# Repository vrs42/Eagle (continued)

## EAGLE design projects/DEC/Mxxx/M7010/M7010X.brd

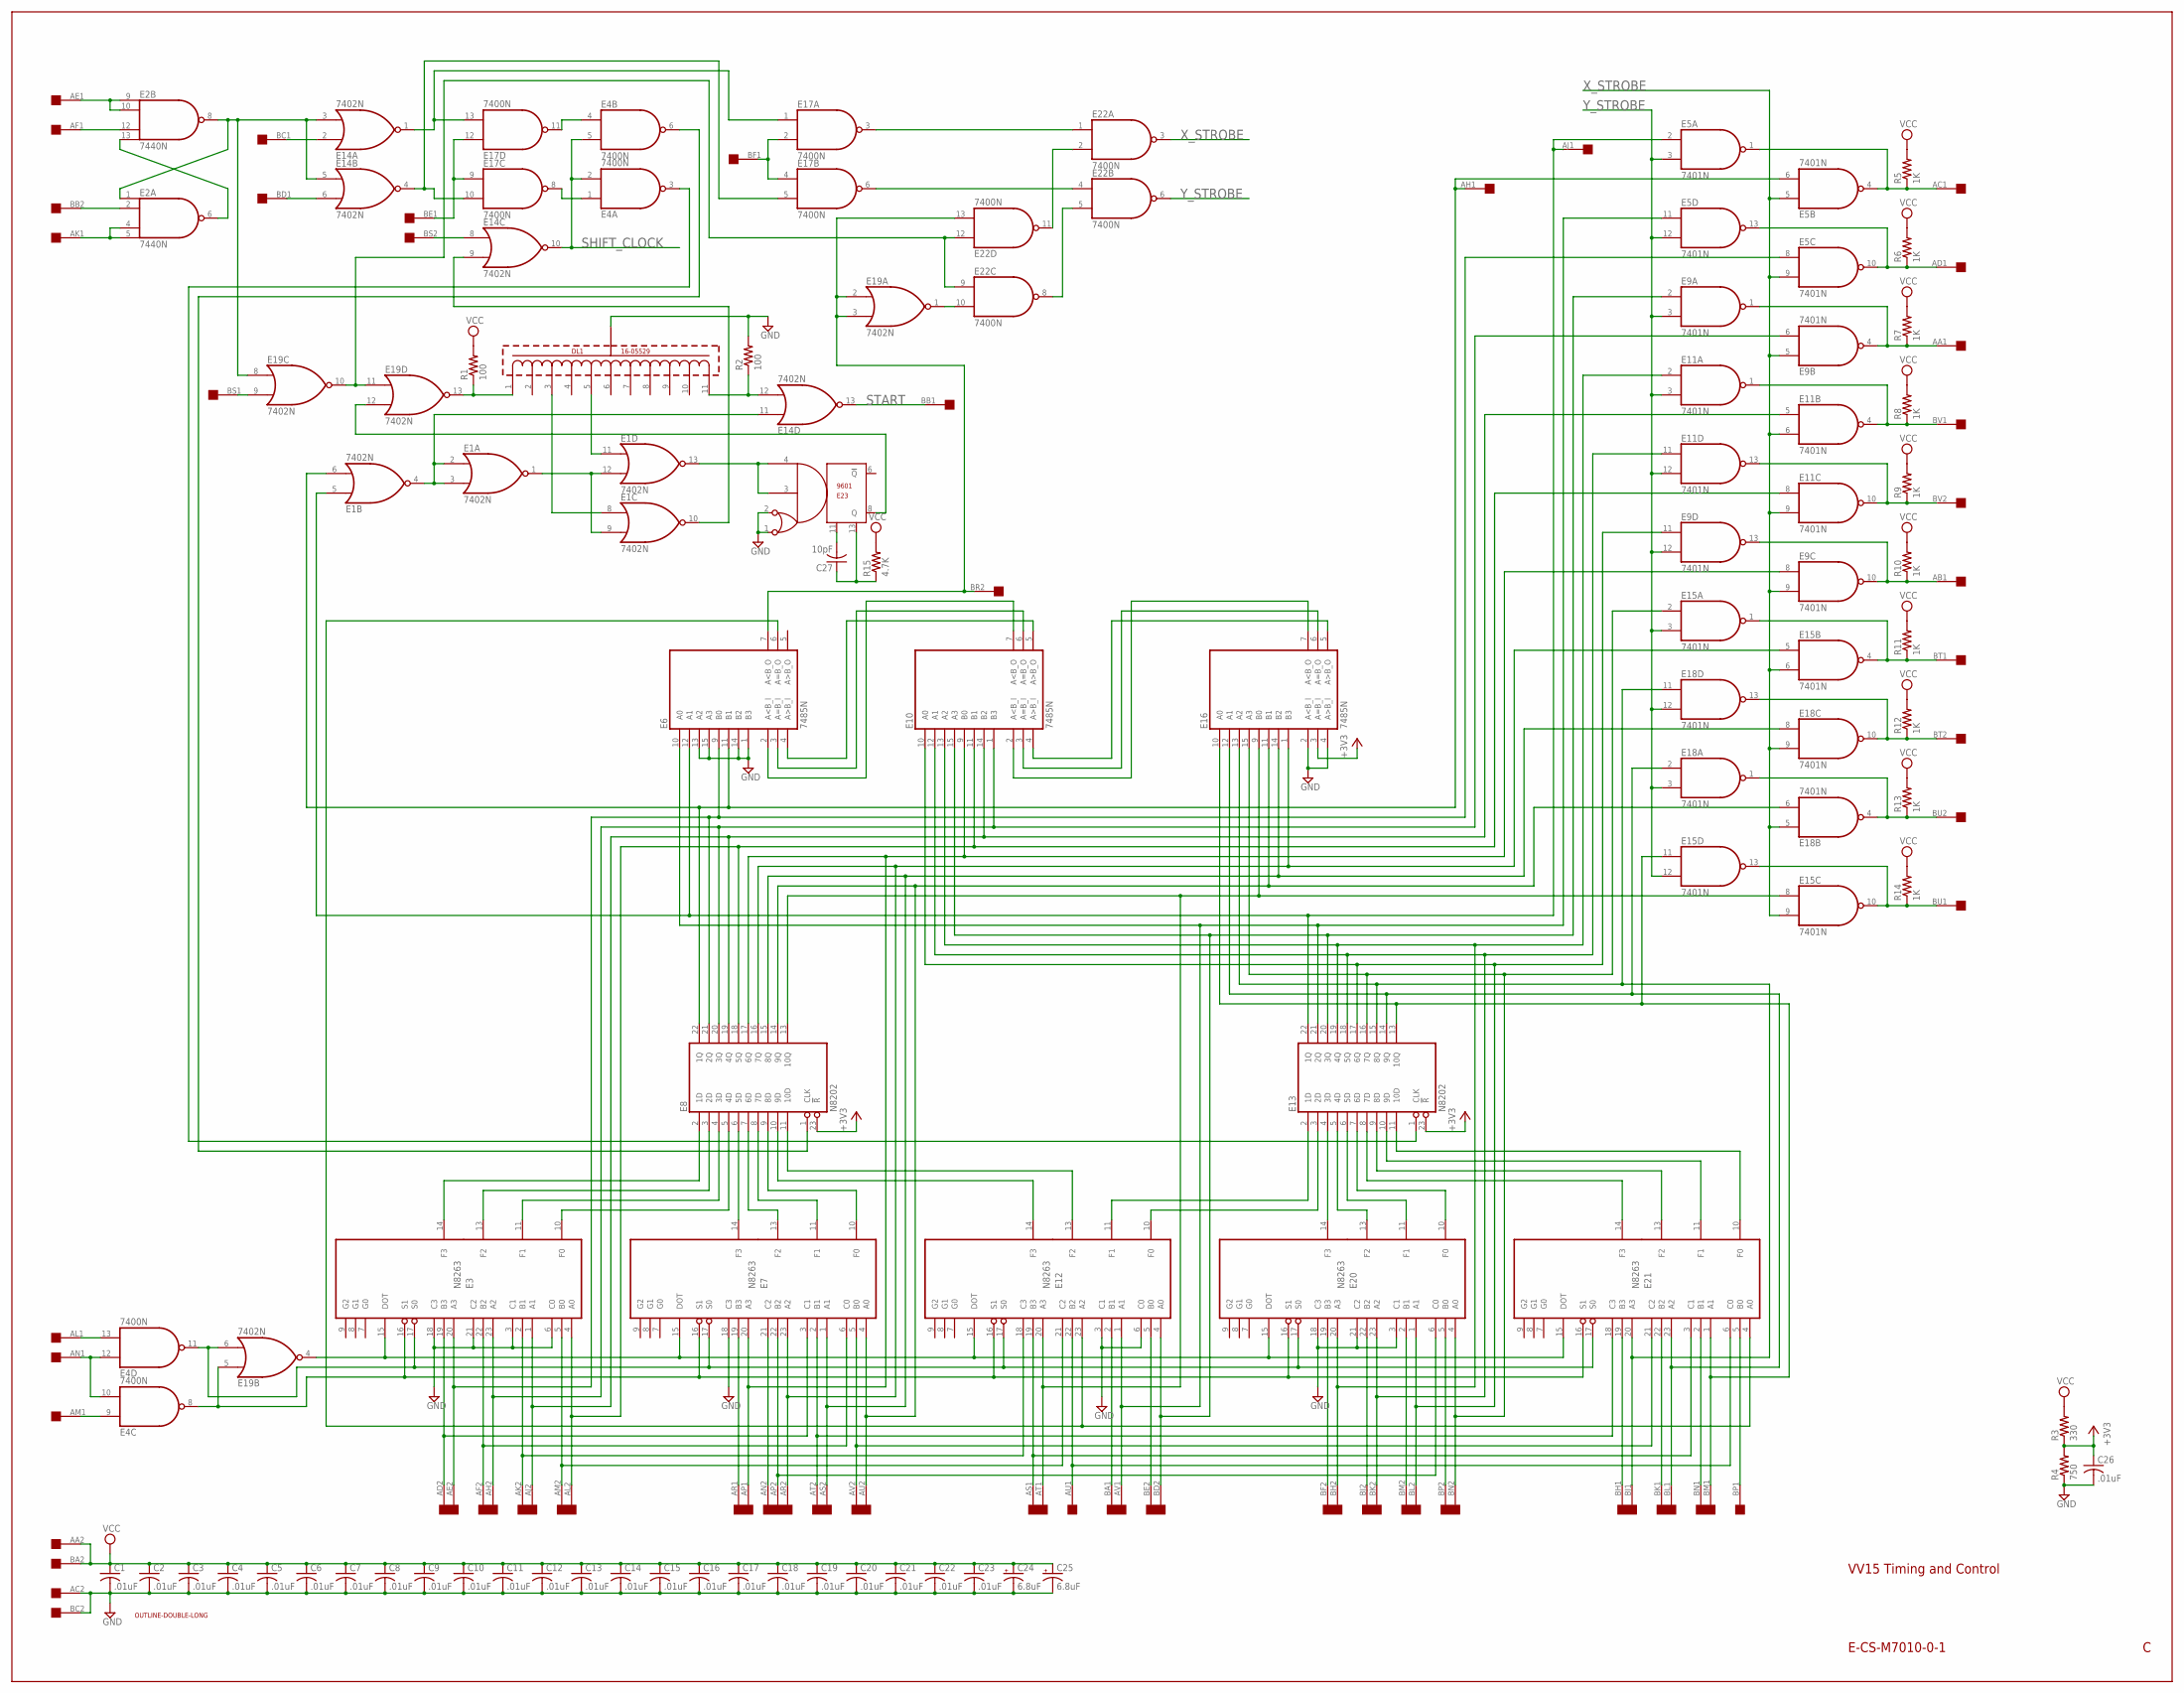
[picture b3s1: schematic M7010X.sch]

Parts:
C1, C2, C3, C4, C5, C6, C7, C8, C9, C10, C11, C12, C13, C14, C15, C16, C17, C18, C19, C20, C21, C22, C23, C26: .01uF; C050-025X075
C24, C25: 6.8uF; E12-8
C27: 10pF; C050-025X075
DL1: 16-05529
E1, E14, E19: 7402N; DIL14
E2: 7440N; DIL14
E3, E7, E12, E20, E21: N8263; DIL24
E4, E17, E22: 7400N; DIL14
E5, E9, E11, E15, E18: 7401N; DIL14
E6, E10, E16: 7485N; DIL16
E8, E13: N8202; DIL24
E23: 9601; DIL14
R1, R2: 100; 0207/10
R3: 330; 0207/10
R4: 750; 0207/10
R5, R6, R7, R8, R9, R10, R11, R12, R13, R14: 1K; 0207/10
R15: 4.7K; 0207/10
U$1: OUTLINE-DOUBLE-LONG; DOUBLE-LONG
U$3: DOUBLE; EDGE-CON4

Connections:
+3V3: C26.1, E8.23 (!R), E13.23 (!R), E16.3 (A=B_I), R3.1, R4.2
GND: C1.2, C2.2, C3.2, C4.2, C5.2, C6.2, C7.2, C8.2, C9.2, C10.2, C11.2, C12.2, C13.2, C14.2, C15.2, C16.2, C17.2, C18.2, C19.2, C20.2, C21.2, C22.2, C23.2, C24.-, C25.-, C26.2, DL1.12 (GND), E1.7 (GND), E2.7 (GND), E3.3 (C1), E3.6 (C0), E3.12 (GND), E3.18 (C3), E3.21 (C2), E4.7 (GND), E5.7 (GND), E6.1 (B3), E6.8 (GND), E6.13 (A2), E6.14 (B2), E6.15 (A3), E7.12 (GND), E7.18 (C3), E8.12 (GND), E9.7 (GND), E10.8 (GND), E11.7 (GND), E12.3 (C1), E12.6 (C0), E12.12 (GND), E13.12 (GND), E14.7 (GND), E15.7 (GND), E16.2 (A<B_I), E16.4 (A>B_I), E16.8 (GND), E17.7 (GND), E18.7 (GND), E19.7 (GND), E20.3 (C1), E20.12 (GND), E20.18 (C3), E20.21 (C2), E21.12 (GND), E22.7 (GND), E23.1, E23.2, E23.7 (GND), R2.2, R4.1, U$3.AC2, U$3.BC2
unnamed: E3.20 (A3), E5.8 (I0), E6.9 (B0), E8.21 (2Q), U$3.AE2
unnamed: E3.23 (A2), E8.20 (3Q), E9.6 (I1), E10.1 (B3), U$3.AH2
unnamed: E3.1 (A1), E8.19 (4Q), E10.14 (B2), E11.5 (I0), U$3.AJ2
unnamed: E3.4 (A0), E8.18 (5Q), E10.11 (B1), E11.8 (I0), U$3.AL2
unnamed: E3.19 (B3), E7.3 (C1), U$3.AD2
unnamed: E3.22 (B2), E7.6 (C0), U$3.AF2
unnamed: E3.2 (B1), E12.18 (C3), U$3.AK2
unnamed: E3.5 (B0), E12.21 (C2), U$3.AM2
unnamed: E7.21 (C2), U$3.AN2
unnamed: E3.15 (DOT), E7.15 (DOT), E12.15 (DOT), E19.4 (O), E20.15 (DOT), E21.15 (DOT)
unnamed: E3.17 (S0), E4.11 (O), E7.17 (S0), E12.17 (S0), E19.6 (I1), E20.17 (S0), E21.17 (S0)
unnamed: E3.16 (S1), E4.8 (O), E7.16 (S1), E12.16 (S1), E19.5 (I0), E20.16 (S1), E21.16 (S1)
unnamed: E7.5 (B0), E21.21 (C2), U$3.AV2
unnamed: E7.2 (B1), E21.18 (C3), U$3.AT2
unnamed: E7.22 (B2), E20.6 (C0), U$3.AP2
unnamed: E7.20 (A3), E8.17 (6Q), E9.8 (I0), E10.9 (B0), U$3.AP1
unnamed: E1.10 (O), E14.9 (I1)
unnamed: E7.1 (A1), E8.15 (8Q), E16.14 (B2), E18.8 (I0), U$3.AS2
unnamed: E7.23 (A2), E8.16 (7Q), E15.5 (I0), E16.1 (B3), U$3.AR2
unnamed: E7.19 (B3), U$3.AR1
unnamed: E7.14 (F3), E8.6 (5D)
unnamed: E7.13 (F2), E8.7 (6D)
unnamed: E7.11 (F1), E8.8 (7D)
unnamed: E7.10 (F0), E8.9 (8D)
unnamed: E3.10 (F0), E8.5 (4D)
unnamed: E3.11 (F1), E8.4 (3D)
unnamed: E3.13 (F2), E8.3 (2D)
unnamed: E3.14 (F3), E8.2 (1D)
unnamed: E8.10 (9D), E12.14 (F3)
unnamed: E8.11 (10D), E12.13 (F2)
unnamed: E13.4 (3D), E20.14 (F3)
unnamed: E13.5 (4D), E20.13 (F2)
unnamed: E13.6 (5D), E20.11 (F1)
unnamed: E13.7 (6D), E20.10 (F0)
unnamed: E12.10 (F0), E13.3 (2D)
unnamed: E12.11 (F1), E13.2 (1D)
unnamed: E13.10 (9D), E21.11 (F1)
unnamed: E13.8 (7D), E21.14 (F3)
unnamed: E13.9 (8D), E21.13 (F2)
unnamed: E13.11 (10D), E21.10 (F0)
unnamed: E5.1 (O), E5.4 (O), R5.1, U$3.AC1
unnamed: E5.10 (O), E5.13 (O), R6.1, U$3.AD1
unnamed: E15.10 (O), E15.13 (O), R14.1, U$3.BU1
unnamed: E18.1 (O), E18.4 (O), R13.1, U$3.BU2
unnamed: E18.10 (O), E18.13 (O), R12.1, U$3.BT2
unnamed: E15.1 (O), E15.4 (O), R11.1, U$3.BT1
unnamed: E9.10 (O), E9.13 (O), R10.1, U$3.AB1
unnamed: E9.1 (O), E9.4 (O), R7.1, U$3.AA1
unnamed: E11.1 (O), E11.4 (O), R8.1, U$3.BV1
unnamed: E11.10 (O), E11.13 (O), R9.1, U$3.BV2
unnamed: E1.2 (I0), E1.3 (I1), E1.4 (O), E14.11 (I0)
unnamed: DL1.11 (50), E14.12 (I1), R2.1
unnamed: E2.1 (I0), E2.8 (O), E14.3 (I1), E14.5 (I0), E19.8 (I0)
unnamed: E1.5 (I0), E5.2 (I0), E6.12 (A1), E13.22 (1Q), U$3.AJ1
unnamed: E1.6 (I1), E5.6 (I1), E6.11 (B1), E8.22 (1Q), U$3.AH1
unnamed: E5.11 (I0), E6.10 (A0), E12.1 (A1), E13.21 (2Q), U$3.AV1
unnamed: E9.2 (I0), E10.15 (A3), E12.4 (A0), E13.20 (3Q), U$3.BD2
unnamed: E10.13 (A2), E11.2 (I0), E13.19 (4Q), E20.20 (A3), U$3.BH2
unnamed: E10.12 (A1), E11.11 (I0), E13.18 (5Q), E20.23 (A2), U$3.BK2
unnamed: E19.9 (I1), U$3.BS1
unnamed: E9.11 (I0), E10.10 (A0), E13.17 (6Q), E20.1 (A1), U$3.BL2
unnamed: E8.13 (10Q), E12.20 (A3), E15.8 (I0), E16.9 (B0), U$3.AT1
unnamed: E13.13 (10Q), E15.11 (I0), E16.10 (A0), E21.1 (A1), U$3.BM1
unnamed: E7.4 (A0), E8.14 (9Q), E16.11 (B1), E18.6 (I1), U$3.AU2
unnamed: E13.14 (9Q), E16.12 (A1), E18.2 (I0), E21.23 (A2), U$3.BL1
unnamed: E13.15 (8Q), E16.13 (A2), E18.11 (I0), E21.20 (A3), U$3.BJ1
unnamed: E13.16 (7Q), E15.2 (I0), E16.15 (A3), E20.4 (A0), U$3.BN2
unnamed: E6.6 (A=B_O), E12.23 (A2), E21.4 (A0)
unnamed: E12.19 (B3), E21.3 (C1), U$3.AS1
unnamed: E12.22 (B2), E21.6 (C0), U$3.AU1
unnamed: E4.13 (I1), U$3.AL1
unnamed: E12.2 (B1), U$3.BA1
unnamed: E12.5 (B0), U$3.BE2
unnamed: E20.19 (B3), U$3.BF2
unnamed: E20.22 (B2), U$3.BJ2
unnamed: E20.2 (B1), U$3.BM2
unnamed: E20.5 (B0), U$3.BP2
unnamed: E21.19 (B3), U$3.BH1
unnamed: E21.22 (B2), U$3.BK1
unnamed: E21.2 (B1), U$3.BN1
unnamed: E21.5 (B0), U$3.BP1
unnamed: E4.9 (I0), U$3.AM1
unnamed: E10.4 (A>B_I), E16.5 (A>B_O)
unnamed: E10.3 (A=B_I), E16.6 (A=B_O)
unnamed: E10.2 (A<B_I), E16.7 (A<B_O)
unnamed: E6.4 (A>B_I), E10.5 (A>B_O)
unnamed: E6.3 (A=B_I), E10.6 (A=B_O)
unnamed: E6.2 (A<B_I), E10.7 (A<B_O)
unnamed: E4.10 (I1), E4.12 (I0), U$3.AN1
unnamed: E14.6 (I1), U$3.BD1
unnamed: E14.2 (I0), U$3.BC1
unnamed: E14.4 (O), E17.5 (I1), E17.10 (I1)
unnamed: E2.9 (I0), E2.10 (I1), U$3.AE1
unnamed: E2.12 (I2), U$3.AF1
unnamed: E2.6 (O), E2.13 (I3)
unnamed: E2.2 (I1), U$3.BB2
unnamed: E2.4 (I2), E2.5 (I3), U$3.AK1
unnamed: E14.1 (O), E17.1 (I0), E17.13 (I1)
unnamed: E17.9 (I0), E17.12 (I0), U$3.BE1
unnamed: E4.1 (I0), E17.8 (O)
unnamed: E4.4 (I0), E17.11 (O)
unnamed: E14.8 (I0), U$3.BS2
unnamed: E19.10 (O), E19.11 (I0), E22.9 (I0), E22.12 (I0)
unnamed: DL1.3 (10), E1.8 (I0)
unnamed: DL1.1 (0), E19.13 (O), R1.1
unnamed: DL1.5 (20), E1.11 (I0)
unnamed: E1.1 (O), E1.9 (I1), E1.12 (I1)
unnamed: C27.2, E23.11
unnamed: E1.13 (O), E23.3, E23.4
unnamed: E19.12 (I1), E23.8 (Q)
unnamed: C27.1, E23.13, R15.1
unnamed: E19.1 (O), E22.10 (I1)
unnamed: E17.3 (O), E22.1 (I0)
unnamed: E17.6 (O), E22.4 (I0)
unnamed: E22.2 (I1), E22.11 (O)
unnamed: E4.3 (O), E13.1 (CLK)
unnamed: E4.6 (O), E8.1 (CLK)
unnamed: E22.5 (I1), E22.8 (O)
unnamed: E17.2 (I1), E17.4 (I0), U$3.BF1
unnamed: E6.7 (A<B_O), E19.2 (I0), E19.3 (I1), E22.13 (I1), U$3.BR2
SHIFT_CLOCK: E4.2 (I1), E4.5 (I1), E14.10 (O)
START: E14.13 (O), U$3.BB1
VCC: C1.1, C2.1, C3.1, C4.1, C5.1, C6.1, C7.1, C8.1, C9.1, C10.1, C11.1, C12.1, C13.1, C14.1, C15.1, C16.1, C17.1, C18.1, C19.1, C20.1, C21.1, C22.1, C23.1, C24.+, C25.+, E1.14 (VCC), E2.14 (VCC), E3.24 (VCC), E4.14 (VCC), E5.14 (VCC), E6.16 (VCC), E7.24 (VCC), E8.24 (VCC), E9.14 (VCC), E10.16 (VCC), E11.14 (VCC), E12.24 (VCC), E13.24 (VCC), E14.14 (VCC), E15.14 (VCC), E16.16 (VCC), E17.14 (VCC), E18.14 (VCC), E19.14 (VCC), E20.24 (VCC), E21.24 (VCC), E22.14 (VCC), E23.14 (VCC), R1.2, R3.2, R5.2, R6.2, R7.2, R8.2, R9.2, R10.2, R11.2, R12.2, R13.2, R14.2, R15.2, U$3.AA2, U$3.BA2
X_STROBE: E5.5 (I0), E5.9 (I1), E9.5 (I0), E9.9 (I1), E11.6 (I1), E11.9 (I1), E15.6 (I1), E15.9 (I1), E18.5 (I0), E18.9 (I1), E22.3 (O)
Y_STROBE: E5.3 (I1), E5.12 (I1), E9.3 (I1), E9.12 (I1), E11.3 (I1), E11.12 (I1), E15.3 (I1), E15.12 (I1), E18.3 (I1), E18.12 (I1), E22.6 (O)

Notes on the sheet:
VV15 Timing and Control
E-CS-M7010-0-1

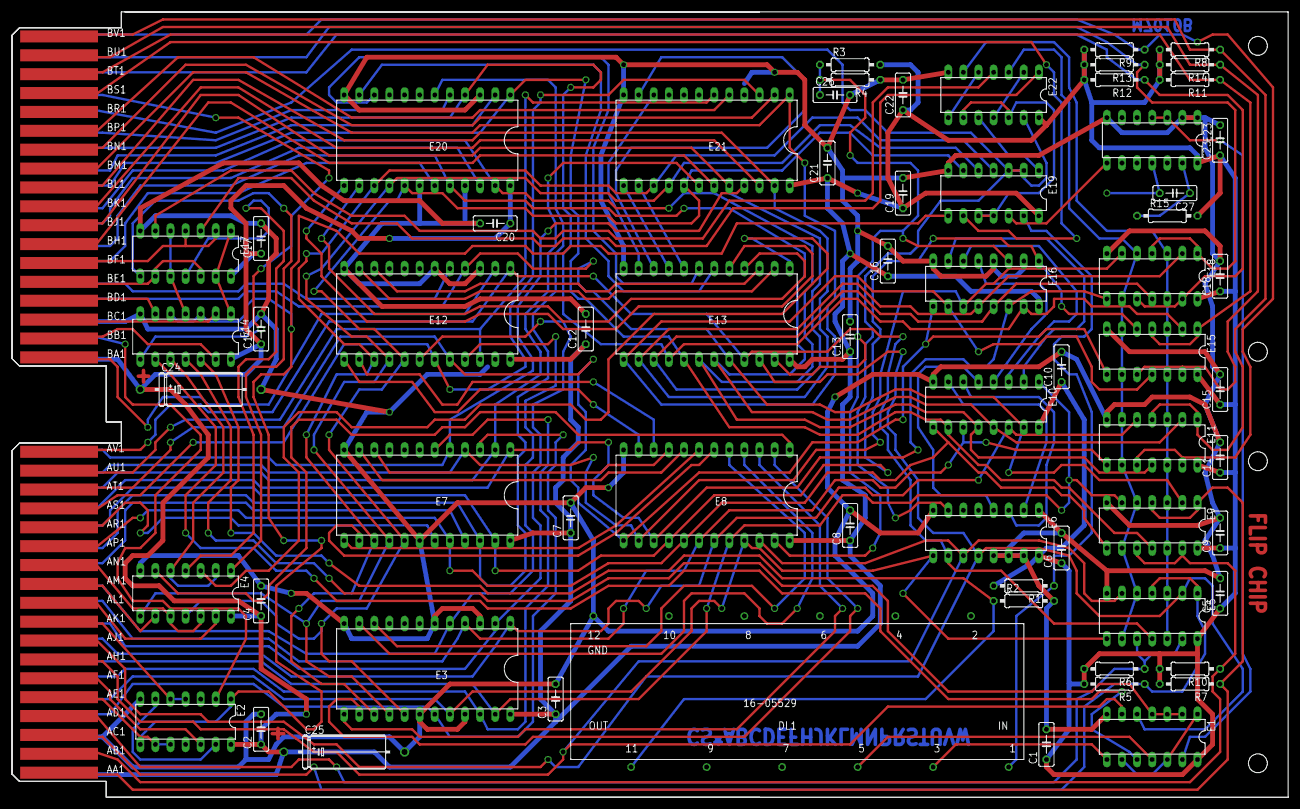
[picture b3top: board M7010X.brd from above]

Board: 3 copper layers, 214.6 x 132.1 mm, 68 parts (0 on the bottom side), 127 nets.

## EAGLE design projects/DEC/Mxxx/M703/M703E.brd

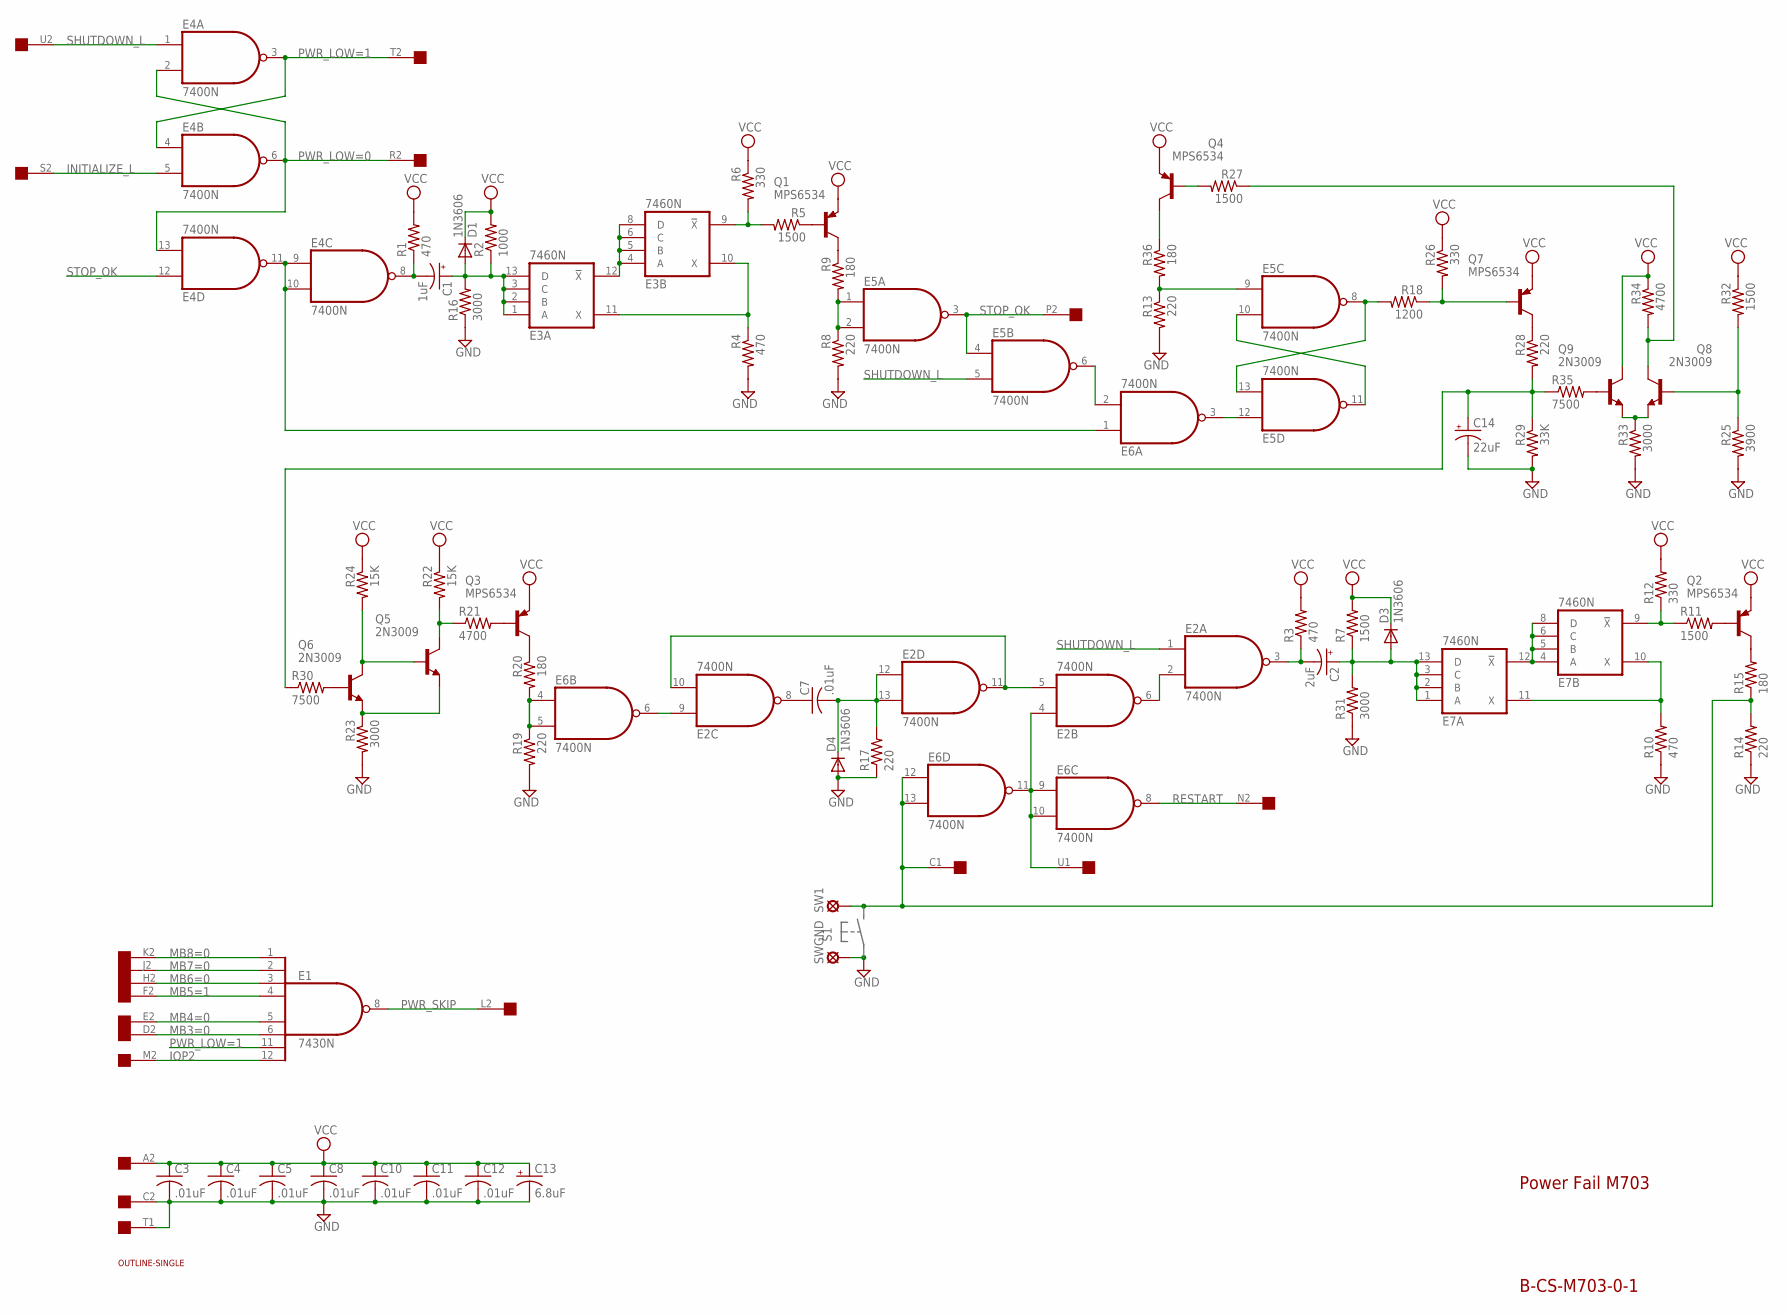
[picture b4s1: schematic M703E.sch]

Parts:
C1: 1uF; E12-4
C2: 2uF; E12-4
C3, C4, C5, C7, C8, C10, C11, C12: .01uF; C050-025X075
C13: 6.8uF; E15-5
C14: 22uF; E15-5
D1, D3, D4: 1N3606; DO35-10
E1: 7430N; DIL14
E2, E4, E5, E6: 7400N; DIL14
E3, E7: 7460N; DIL14
Q1, Q2, Q3, Q4, Q7: MPS6534; TO39
Q5, Q6, Q8, Q9: 2N3009; TO5
R1, R3, R4, R10: 470; 0207/10
R2: 1000; 0207/10
R5, R7, R11, R27, R32: 1500; 0207/10
R6, R12, R26: 330; 0207/10
R8, R13, R14, R17, R19, R28: 220; 0207/10
R9, R15, R20, R36: 180; 0207/10
R16, R23, R31, R33: 3000; 0207/10
R18: 1200; 0207/10
R21, R34: 4700; 0207/10
R22, R24: 15K; 0207/10
R25: 3900; 0207/10
R29: 33K; 0207/10
R30, R35: 7500; 0207/10
SW1: SE14
SWGND: SE14
U$2: SINGLE; EDGE-CON2
U$4: OUTLINE-SINGLE; SINGLE

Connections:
GND: C3.2, C4.2, C5.2, C8.2, C10.2, C11.2, C12.2, C13.-, C14.-, D4.A, E1.7 (GND), E2.7 (GND), E3.7 (GND), E4.7 (GND), E5.7 (GND), E6.7 (GND), E7.7 (GND), R4.2, R8.2, R10.1, R13.2, R14.1, R16.1, R17.1, R19.2, R23.2, R25.2, R29.2, R31.1, R33.2, SWGND.MP, U$2.C2, U$2.T1
INITIALIZE_L: E4.5 (I1), U$2.S2
IOP2: E1.12 (I7), U$2.M2
MB3=0: E1.6 (I5), U$2.D2
MB4=0: E1.5 (I4), U$2.E2
MB5=1: E1.4 (I3), U$2.F2
MB6=0: E1.3 (I2), U$2.H2
MB7=0: E1.2 (I1), U$2.J2
MB8=0: E1.1 (I0), U$2.K2
unnamed: E4.9 (I0), E4.10 (I1), E4.11 (O), E6.1 (I0)
unnamed: E2.4 (I0), E6.9 (I0), E6.10 (I1), E6.11 (O), U$2.U1
unnamed: C1.-, E4.8 (O), R1.1
unnamed: E6.4 (I0), E6.5 (I1), R19.1, R20.2
unnamed: E3.4 (A), E3.5 (B), E3.6 (C), E3.8 (D), E3.12 (!X)
unnamed: C1.+, D1.A, E3.1 (A), E3.2 (B), E3.3 (C), E3.13 (D), R2.1, R16.2
unnamed: C2.+, D3.A, E7.1 (A), E7.2 (B), E7.3 (C), E7.13 (D), R7.1, R31.2
unnamed: E7.4 (A), E7.5 (B), E7.6 (C), E7.8 (D), E7.12 (!X)
unnamed: E5.1 (I0), E5.2 (I1), R8.1, R9.2
unnamed: C7.2, D4.C, E2.12 (I0), E2.13 (I1), R17.2
unnamed: E2.5 (I1), E2.10 (I1), E2.11 (O)
unnamed: C7.1, E2.8 (O)
unnamed: E2.2 (I1), E2.6 (O)
unnamed: E5.8 (O), E5.13 (I1), R18.2
unnamed: C2.-, E2.3 (O), R3.1
unnamed: E6.12 (I0), E6.13 (I1), R14.2, R15.1, SW1.MP, U$2.C1
unnamed: E2.9 (I0), E6.6 (O)
unnamed: E5.12 (I0), E6.3 (O)
unnamed: E5.6 (O), E6.2 (I1)
unnamed: Q1.2 (B), R5.1
unnamed: Q1.3 (C), R9.1
unnamed: E7.9 (!X), R11.1, R12.1
unnamed: E7.10 (X), E7.11 (X), R10.2
unnamed: Q2.2 (B), R11.2
unnamed: E3.10 (X), E3.11 (X), R4.1
unnamed: Q4.3 (C), R36.1
unnamed: E3.9 (!X), R5.2, R6.2
unnamed: E5.10 (I1), E5.11 (O)
unnamed: E5.9 (I0), R13.1, R36.2
unnamed: Q7.2 (B), R18.1, R26.2
unnamed: Q8.1 (E), Q9.1 (E), R33.1
unnamed: Q8.3 (C), R27.1, R34.2
unnamed: Q4.2 (B), R27.2
unnamed: Q8.2 (B), R25.1, R32.2
unnamed: Q9.2 (B), R35.2
unnamed: Q7.3 (C), R28.1
unnamed: C14.+, R28.2, R29.1, R30.1, R35.1
unnamed: Q6.2 (B), R30.2
unnamed: Q5.2 (B), Q6.3 (C), R24.2
unnamed: Q5.1 (E), Q6.1 (E), R23.1
unnamed: Q5.3 (C), R21.1, R22.2
unnamed: Q3.2 (B), R21.2
unnamed: Q3.3 (C), R20.1
unnamed: Q2.3 (C), R15.2
PWR_LOW=0: E4.2 (I1), E4.6 (O), E4.13 (I1), U$2.R2
PWR_LOW=1: E1.11 (I6), E4.3 (O), E4.4 (I0), U$2.T2
PWR_SKIP: E1.8 (O), U$2.L2
RESTART: E6.8 (O), U$2.N2
SHUTDOWN_L: E2.1 (I0), E4.1 (I0), E5.5 (I1), U$2.U2
STOP_OK: E4.12 (I0), E5.3 (O), E5.4 (I0), U$2.P2
VCC: C3.1, C4.1, C5.1, C8.1, C10.1, C11.1, C12.1, C13.+, D1.C, D3.C, E1.14 (VCC), E2.14 (VCC), E3.14 (VCC), E4.14 (VCC), E5.14 (VCC), E6.14 (VCC), E7.14 (VCC), Q1.1 (E), Q2.1 (E), Q3.1 (E), Q4.1 (E), Q7.1 (E), Q9.3 (C), R1.2, R2.2, R3.2, R6.1, R7.2, R12.2, R22.1, R24.1, R26.1, R32.1, R34.1, U$2.A2

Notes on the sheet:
Power Fail M703
B-CS-M703-0-1

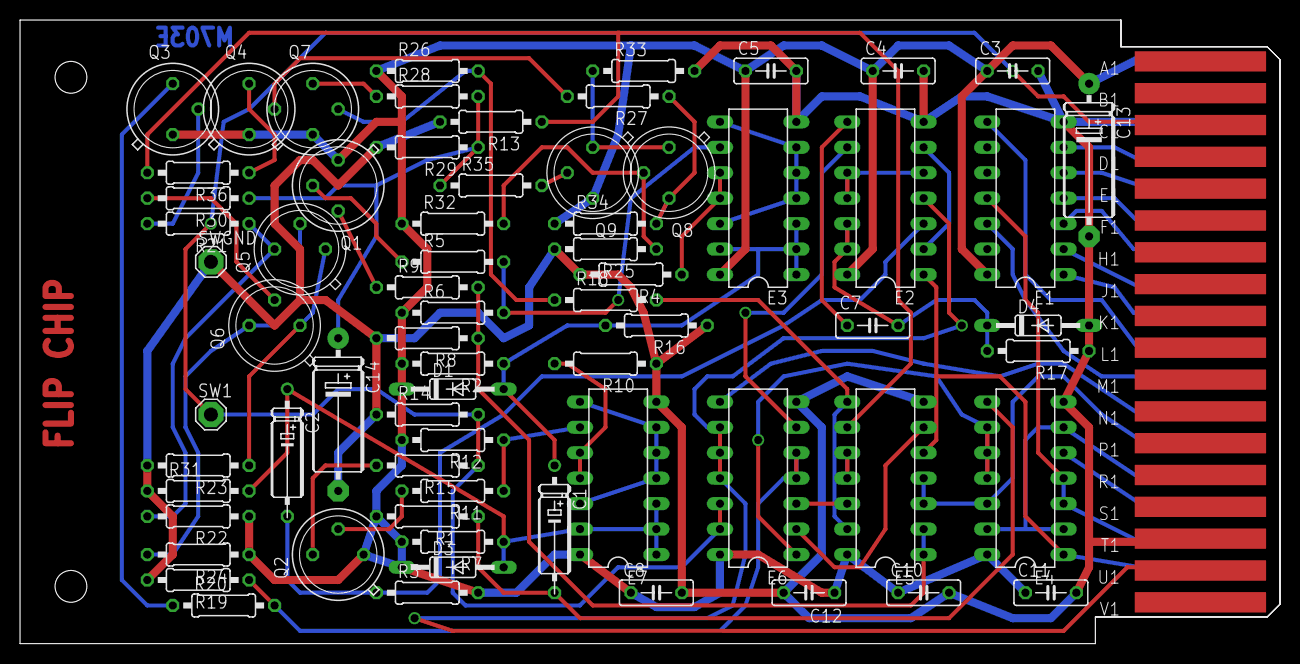
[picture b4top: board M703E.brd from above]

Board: 2 copper layers, 125.7 x 62.2 mm, 72 parts (0 on the bottom side), 60 nets.

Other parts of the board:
U$1: FLIPCHIP

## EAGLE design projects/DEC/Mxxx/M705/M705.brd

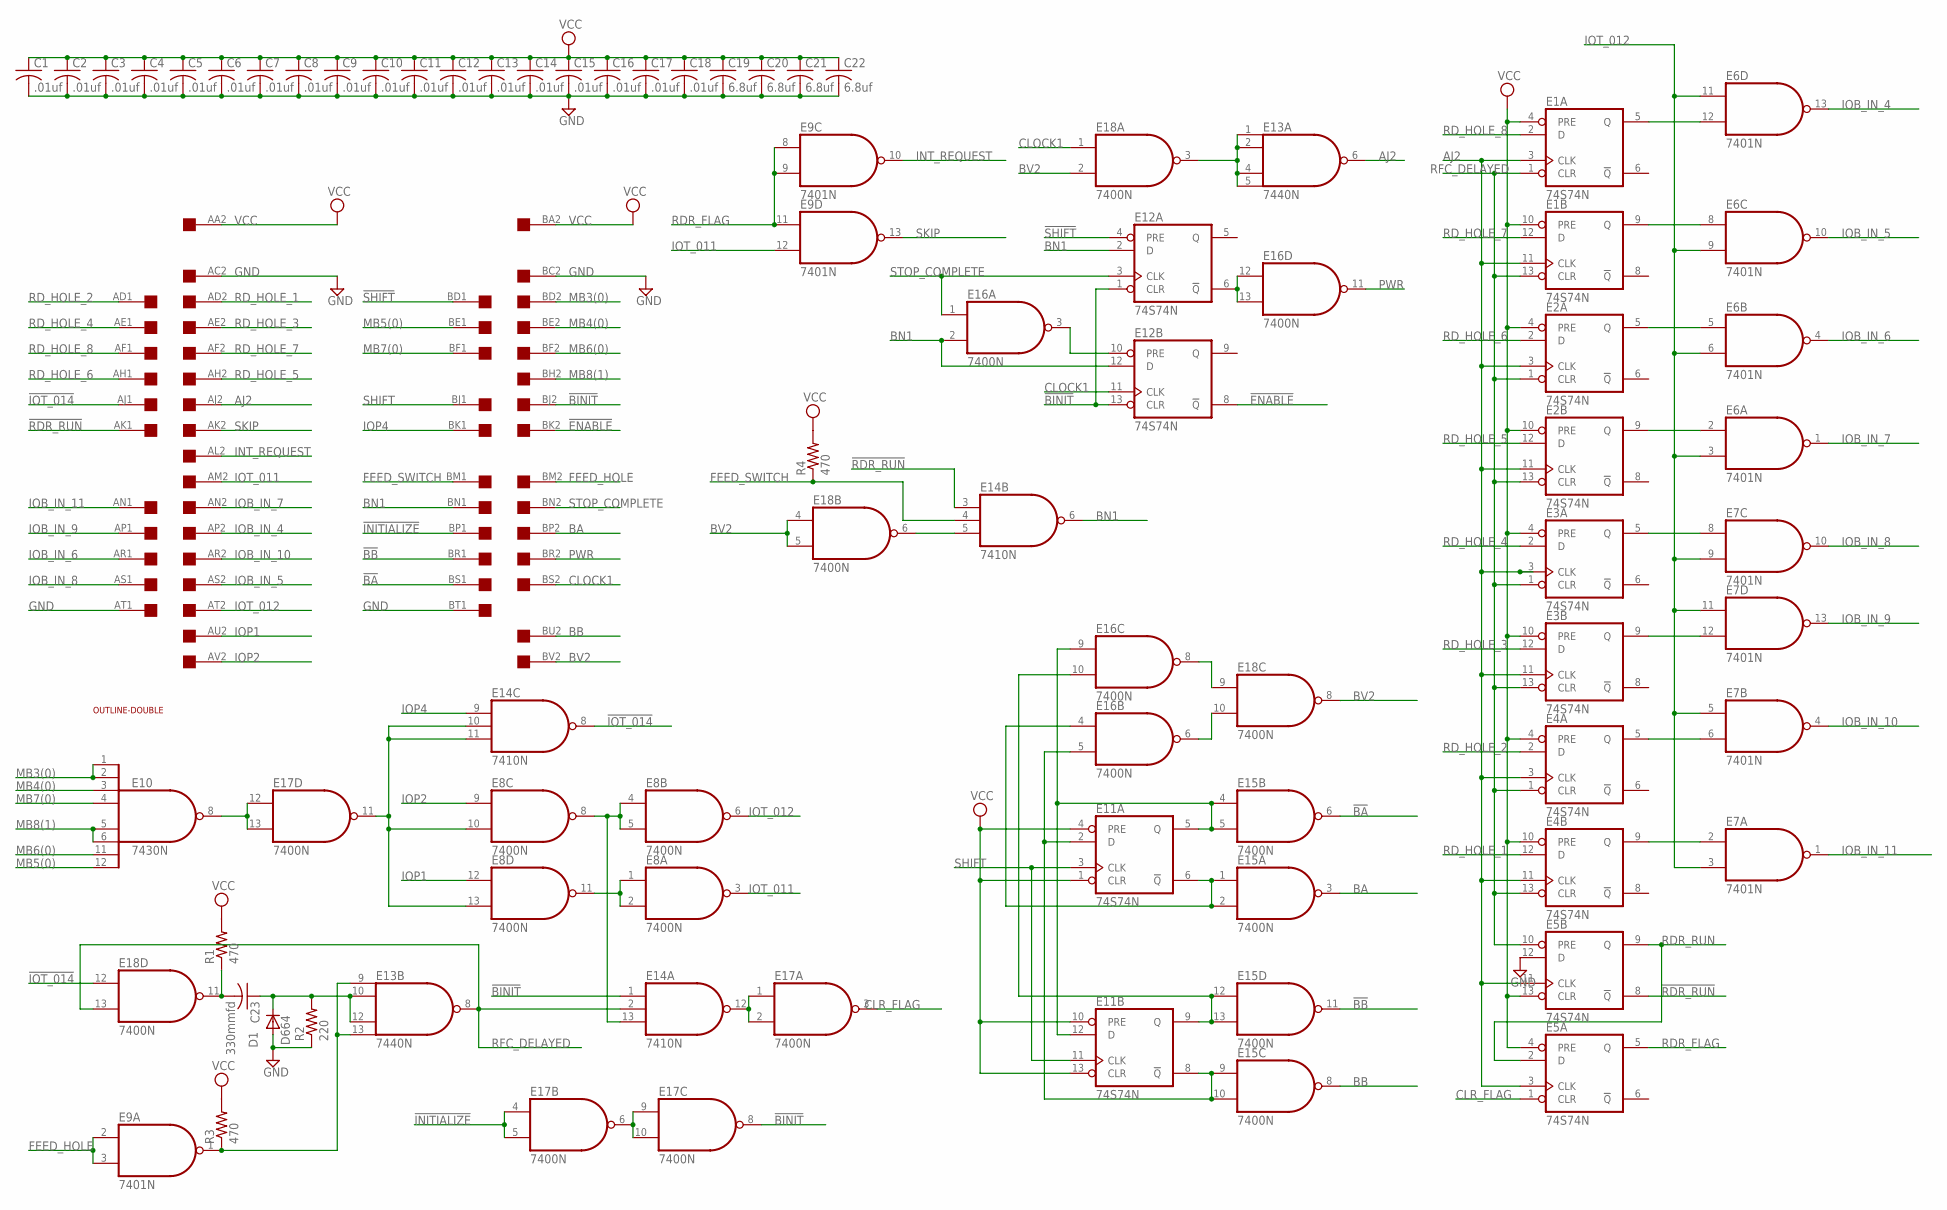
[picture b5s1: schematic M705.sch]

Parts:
C1, C2, C3, C4, C5, C6, C7, C8, C9, C10, C11, C12, C13, C14, C15, C16, C17, C18: .01uf; C050-025X075
C19, C20, C21, C22: 6.8uf; C150-054X183
C23: 330mmfd; C050-025X075
D1: D664; DO35-10
E1, E2, E3, E4, E5, E11, E12: 74S74N; DIL14
E6, E7, E9: 7401N; DIL14
E8, E15, E16, E17, E18: 7400N; DIL14
E10: 7430N; DIL14
E13: 7440N; DIL14
E14: 7410N; DIL14
R1, R3, R4: 470; 0207/10
R2: 220; 0207/10
U$5: DOUBLE; EDGE-CON4
U$6: OUTLINE-DOUBLE; DOUBLE

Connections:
!BA: E15.6 (O), U$5.BS1
!BB: E15.11 (O), U$5.BR1
!BINIT: E12.1 (CLR), E12.13 (CLR), E14.1 (I0), E17.8 (O), U$5.BJ2
!ENABLE: E12.8 (!Q), U$5.BK2
!INITIALIZE: E17.4 (I0), E17.5 (I1), U$5.BP1
!IOT_014: E14.8 (O), E18.12 (I0), U$5.AJ1
!RDR_RUN: E5.8 (!Q), E14.3 (I0), U$5.AK1
!SHIFT: E12.4 (PRE), U$5.BD1
AJ2: E1.3 (CLK), E1.11 (CLK), E2.3 (CLK), E2.11 (CLK), E3.3 (CLK), E3.11 (CLK), E4.3 (CLK), E4.11 (CLK), E5.3 (CLK), E5.11 (CLK), E13.6 (O), U$5.AJ2
BA: E15.3 (O), U$5.BP2
BB: E15.8 (O), U$5.BU2
BN1: E12.2 (D), E12.12 (D), E14.6 (O), E16.2 (I1), U$5.BN1
BV2: E18.2 (I1), E18.4 (I0), E18.5 (I1), E18.8 (O), U$5.BV2
CLOCK1: E12.11 (CLK), E18.1 (I0), U$5.BS2
CLR_FLAG: E5.1 (CLR), E17.3 (O)
FEED_HOLE: E9.2 (I0), E9.3 (I1), U$5.BM2
FEED_SWITCH: E14.4 (I1), R4.1, U$5.BM1
GND: C1.2, C2.2, C3.2, C4.2, C5.2, C6.2, C7.2, C8.2, C9.2, C10.2, C11.2, C12.2, C13.2, C14.2, C15.2, C16.2, C17.2, C18.2, C19.2, C20.2, C21.2, C22.2, D1.A, E1.7 (GND), E2.7 (GND), E3.7 (GND), E4.7 (GND), E5.7 (GND), E5.12 (D), E6.7 (GND), E7.7 (GND), E8.7 (GND), E9.7 (GND), E10.7 (GND), E11.7 (GND), E12.7 (GND), E13.7 (GND), E14.7 (GND), E15.7 (GND), E16.7 (GND), E17.7 (GND), E18.7 (GND), R2.1, U$5.AC2, U$5.AT1, U$5.BC2, U$5.BT1
INT_REQUEST: E9.10 (O), U$5.AL2
IOB_IN_4: E6.13 (O), U$5.AP2
IOB_IN_5: E6.10 (O), U$5.AS2
IOB_IN_6: E6.4 (O), U$5.AR1
IOB_IN_7: E6.1 (O), U$5.AN2
IOB_IN_8: E7.10 (O), U$5.AS1
IOB_IN_9: E7.13 (O), U$5.AP1
IOB_IN_10: E7.4 (O), U$5.AR2
IOB_IN_11: E7.1 (O), U$5.AN1
IOP1: E8.12 (I0), U$5.AU2
IOP2: E8.9 (I0), U$5.AV2
IOP4: E14.9 (I0), U$5.BK1
IOT_011: E8.3 (O), E9.12 (I1), U$5.AM2
IOT_012: E6.3 (I1), E6.6 (I1), E6.9 (I1), E6.11 (I0), E7.3 (I1), E7.5 (I0), E7.9 (I1), E7.11 (I0), E8.6 (O), U$5.AT2
MB3(0): E10.1 (I0), E10.2 (I1), U$5.BD2
MB4(0): E10.3 (I2), U$5.BE2
MB5(0): E10.12 (I7), U$5.BE1
MB6(0): E10.11 (I6), U$5.BF2
MB7(0): E10.4 (I3), U$5.BF1
MB8(1): E10.5 (I4), E10.6 (I5), U$5.BH2
unnamed: E1.5 (Q), E6.12 (I1)
unnamed: E1.9 (Q), E6.8 (I0)
unnamed: E11.6 (!Q), E15.1 (I0), E15.2 (I1), E16.4 (I0)
unnamed: E10.8 (O), E17.12 (I0), E17.13 (I1)
unnamed: E8.4 (I0), E8.5 (I1), E8.8 (O), E14.13 (I2)
unnamed: E8.1 (I0), E8.2 (I1), E8.11 (O)
unnamed: E8.10 (I1), E8.13 (I1), E14.10 (I1), E14.11 (I2), E17.11 (O)
unnamed: E2.5 (Q), E6.5 (I0)
unnamed: E2.9 (Q), E6.2 (I0)
unnamed: E3.5 (Q), E7.8 (I0)
unnamed: E3.9 (Q), E7.12 (I1)
unnamed: E4.5 (Q), E7.6 (I1)
unnamed: E4.9 (Q), E7.2 (I0)
unnamed: E11.5 (Q), E11.12 (D), E15.4 (I0), E15.5 (I1), E16.9 (I0)
unnamed: E11.9 (Q), E15.12 (I0), E15.13 (I1), E16.10 (I1)
unnamed: E11.2 (D), E11.8 (!Q), E15.9 (I0), E15.10 (I1), E16.5 (I1)
unnamed: E16.8 (O), E18.9 (I0)
unnamed: E16.6 (O), E18.10 (I1)
unnamed: E13.1 (I0), E13.2 (I1), E13.4 (I2), E13.5 (I3), E18.3 (O)
unnamed: E12.6 (!Q), E16.12 (I0), E16.13 (I1)
unnamed: E12.10 (PRE), E16.3 (O)
unnamed: C23.2, E18.11 (O), R1.1
unnamed: C23.1, D1.C, E13.10 (I1), E13.12 (I2), R2.2
unnamed: E9.1 (O), E13.9 (I0), E13.13 (I3), R3.1
unnamed: E17.6 (O), E17.9 (I0), E17.10 (I1)
unnamed: E14.12 (O), E17.1 (I0), E17.2 (I1)
unnamed: E14.5 (I2), E18.6 (O)
PWR: E16.11 (O), U$5.BR2
RDR_FLAG: E5.5 (Q), E9.8 (I0), E9.9 (I1), E9.11 (I0)
RDR_RUN: E5.2 (D), E5.9 (Q)
RD_HOLE_1: E4.12 (D), U$5.AD2
RD_HOLE_2: E4.2 (D), U$5.AD1
RD_HOLE_3: E3.12 (D), U$5.AE2
RD_HOLE_4: E3.2 (D), U$5.AE1
RD_HOLE_5: E2.12 (D), U$5.AH2
RD_HOLE_6: E2.2 (D), U$5.AH1
RD_HOLE_7: E1.12 (D), U$5.AF2
RD_HOLE_8: E1.2 (D), U$5.AF1
RFC_DELAYED: E1.1 (CLR), E1.13 (CLR), E2.1 (CLR), E2.13 (CLR), E3.1 (CLR), E3.13 (CLR), E4.1 (CLR), E4.13 (CLR), E5.10 (PRE), E13.8 (O), E14.2 (I1), E18.13 (I1)
SHIFT: E11.3 (CLK), E11.11 (CLK), U$5.BJ1
SKIP: E9.13 (O), U$5.AK2
STOP_COMPLETE: E12.3 (CLK), E16.1 (I0), U$5.BN2
VCC: C1.1, C2.1, C3.1, C4.1, C5.1, C6.1, C7.1, C8.1, C9.1, C10.1, C11.1, C12.1, C13.1, C14.1, C15.1, C16.1, C17.1, C18.1, C19.1, C20.1, C21.1, C22.1, E1.4 (PRE), E1.10 (PRE), E1.14 (VCC), E2.4 (PRE), E2.10 (PRE), E2.14 (VCC), E3.4 (PRE), E3.10 (PRE), E3.14 (VCC), E4.4 (PRE), E4.10 (PRE), E4.14 (VCC), E5.4 (PRE), E5.13 (CLR), E5.14 (VCC), E6.14 (VCC), E7.14 (VCC), E8.14 (VCC), E9.14 (VCC), E10.14 (VCC), E11.1 (CLR), E11.4 (PRE), E11.10 (PRE), E11.13 (CLR), E11.14 (VCC), E12.14 (VCC), E13.14 (VCC), E14.14 (VCC), E15.14 (VCC), E16.14 (VCC), E17.14 (VCC), E18.14 (VCC), R1.2, R3.2, R4.2, U$5.AA2, U$5.BA2

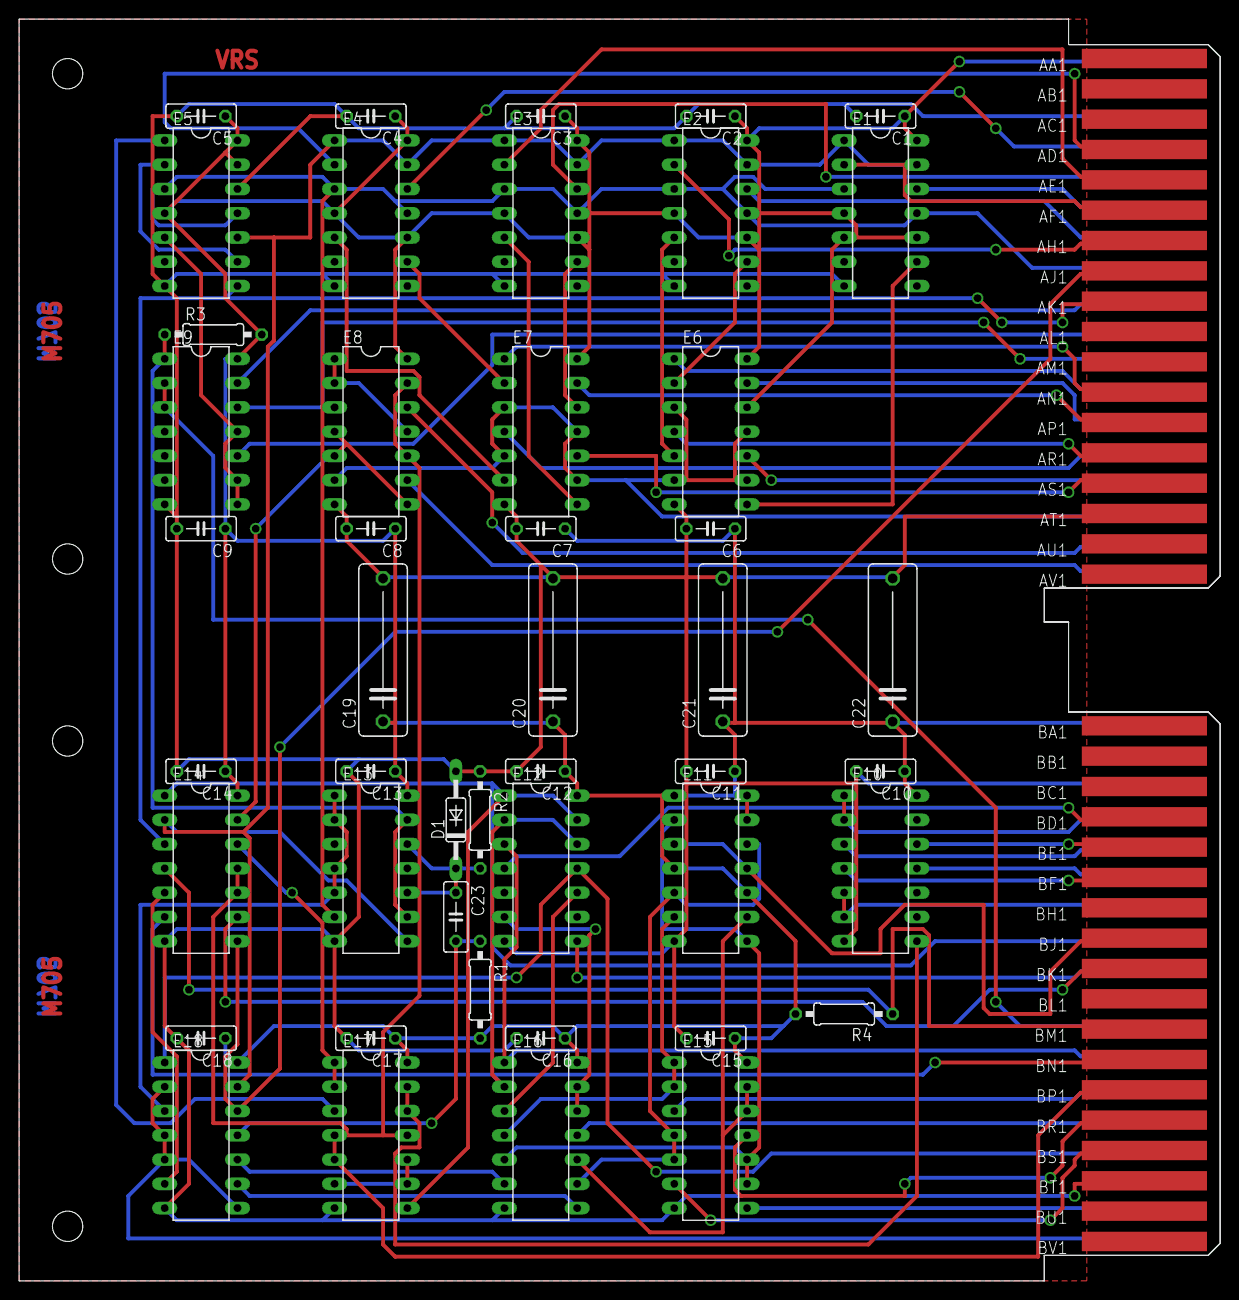
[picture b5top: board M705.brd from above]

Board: 2 copper layers, 125.7 x 132.1 mm, 48 parts (0 on the bottom side), 81 nets.
